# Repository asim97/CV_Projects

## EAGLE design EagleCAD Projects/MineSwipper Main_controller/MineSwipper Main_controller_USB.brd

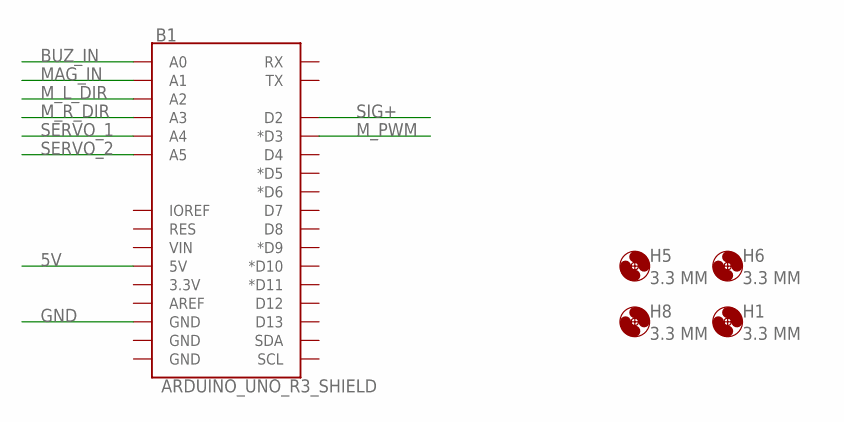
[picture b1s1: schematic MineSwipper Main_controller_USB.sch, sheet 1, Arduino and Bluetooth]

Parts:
B1: ARDUINO_UNO_R3_SHIELD; UNO_R3_SHIELD_NOLABELS_LOCK
H1, H5, H6, H8: 3.3 MM; 3,3

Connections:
5V: B1.5V; also elsewhere on the board
BUZ_IN: B1.A0; also elsewhere on the board
GND: B1.GND@2 (GND); also elsewhere on the board
MAG_IN: B1.A1; also elsewhere on the board
M_L_DIR: B1.A2; also elsewhere on the board
M_PWM: B1.D3 (*D3); also elsewhere on the board
M_R_DIR: B1.A3; also elsewhere on the board
SERVO_1: B1.A4; also elsewhere on the board
SERVO_2: B1.A5; also elsewhere on the board
SIG+: B1.D2; also elsewhere on the board

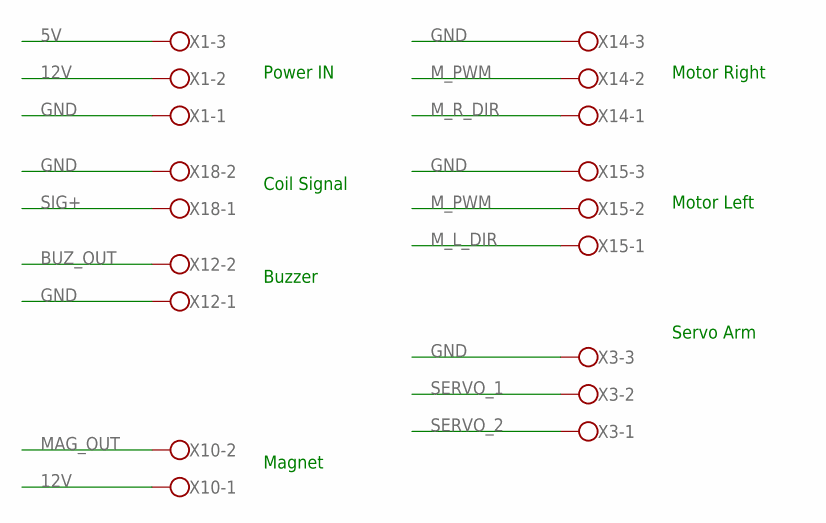
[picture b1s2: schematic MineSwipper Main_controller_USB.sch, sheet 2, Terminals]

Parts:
X1, X3, X14, X15: W237-103
X10, X12, X18: W237-102

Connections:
5V: X1.3; also elsewhere on the board
12V: X1.2, X10.1; also elsewhere on the board
BUZ_OUT: X12.2; also elsewhere on the board
GND: X1.1, X3.3, X12.1, X14.3, X15.3, X18.2; also elsewhere on the board
MAG_OUT: X10.2; also elsewhere on the board
M_L_DIR: X15.1; also elsewhere on the board
M_PWM: X14.2, X15.2; also elsewhere on the board
M_R_DIR: X14.1; also elsewhere on the board
SERVO_1: X3.2; also elsewhere on the board
SERVO_2: X3.1; also elsewhere on the board
SIG+: X18.1; also elsewhere on the board

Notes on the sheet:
Motor Right
Motor Left
Servo Arm
Power IN
Buzzer
Magnet
Coil Signal

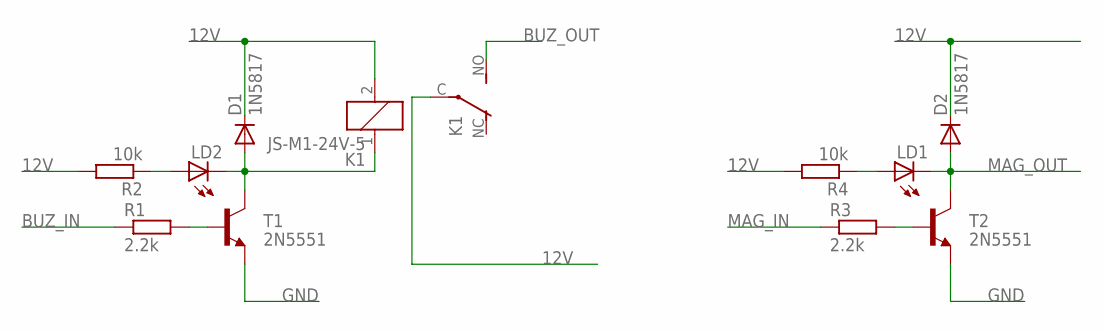
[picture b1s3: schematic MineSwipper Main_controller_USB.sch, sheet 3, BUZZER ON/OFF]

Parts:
D1, D2: 1N5817; DO41-10
K1: JS-M1-24V-5; JS-M
LD1, LD2: LED5MM
R1, R3: 2.2k; 0207/10
R2, R4: 10k; 0207/10
T1, T2: 2N5551; TO92-EBC-OVAL

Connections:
12V: D1.C, D2.C, K1.2, K1.C, R2.2, R4.2; also elsewhere on the board
BUZ_IN: R1.1; also elsewhere on the board
BUZ_OUT: K1.NO (S); also elsewhere on the board
GND: T1.E, T2.E; also elsewhere on the board
MAG_IN: R3.1; also elsewhere on the board
MAG_OUT: D2.A, LD1.K (C), T2.C; also elsewhere on the board
unnamed: R3.2, T2.B
unnamed: LD1.A, R4.1
unnamed: D1.A, K1.1, LD2.K (C), T1.C
unnamed: R1.2, T1.B
unnamed: LD2.A, R2.1

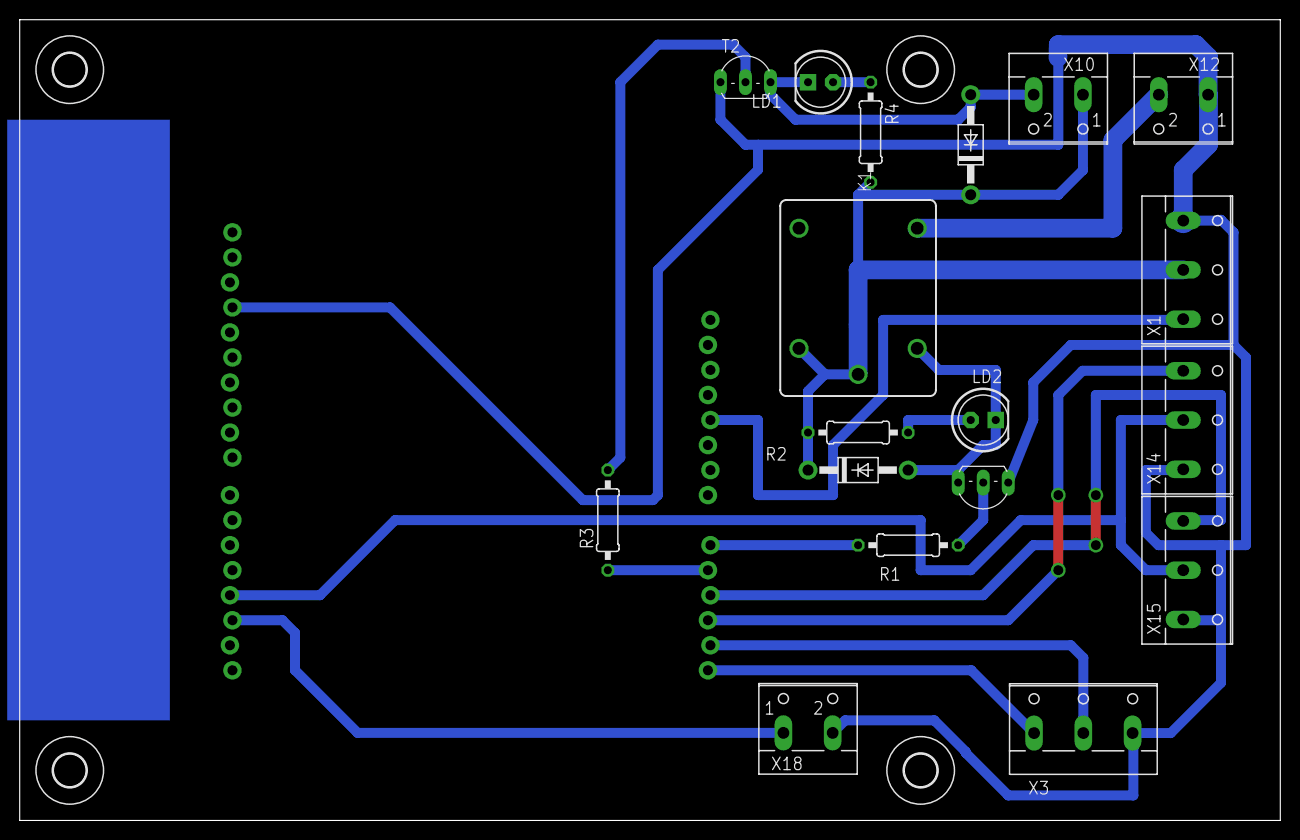
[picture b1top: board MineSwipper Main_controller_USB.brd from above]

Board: 2 copper layers, 127.9 x 81.3 mm, 23 parts (1 on the bottom side), 18 nets.

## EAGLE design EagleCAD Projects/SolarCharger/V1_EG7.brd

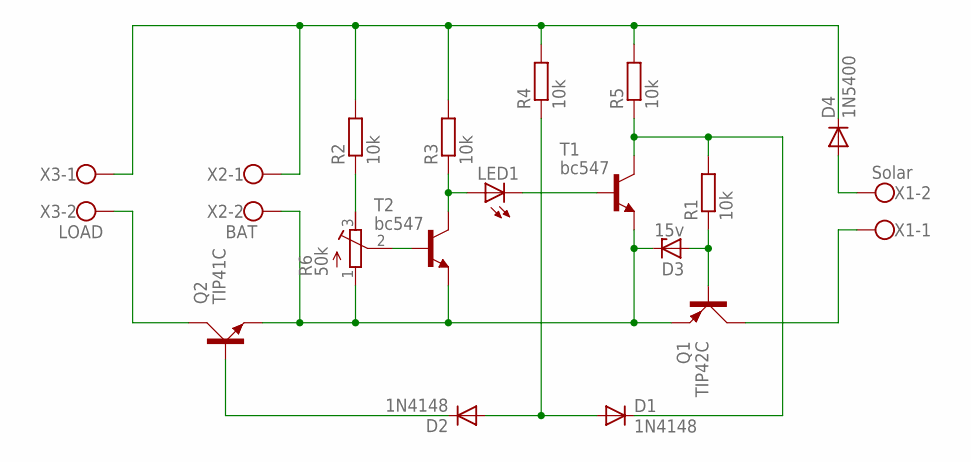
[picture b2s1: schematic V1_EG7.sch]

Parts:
D1, D2: 1N4148; DO35-10
D3: 15v; ZDIO-10
D4: 1N5400; DO201-15
LED1: LED5MM
Q1: TIP42C; TO220AV
Q2: TIP41C; TO220AV
R1, R2, R3, R4, R5: 10k; 0207/10
R6: 50k; RTRIM64W
T1, T2: bc547; TO92-CBE
X1: Solar; W237-102
X2: BAT; W237-102
X3: LOAD; W237-102

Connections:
GND: D3.C, Q1.E, Q2.E, R6.1 (A), T1.E, T2.E, X2.2
unnamed: R6.2 (S), T2.B
unnamed: R2.1, R6.3 (E)
unnamed: LED1.A, R3.1, T2.C
unnamed: LED1.K (C), T1.B
unnamed: D1.C, R1.2, R5.1, T1.C
unnamed: D3.A, Q1.B, R1.1
unnamed: D1.A, D2.A, R4.1
unnamed: Q2.C, X3.2
unnamed: Q1.C, X1.1
unnamed: D2.C, Q2.B
unnamed: D4.C, R2.2, R3.2, R4.2, R5.2, X2.1, X3.1
unnamed: D4.A, X1.2

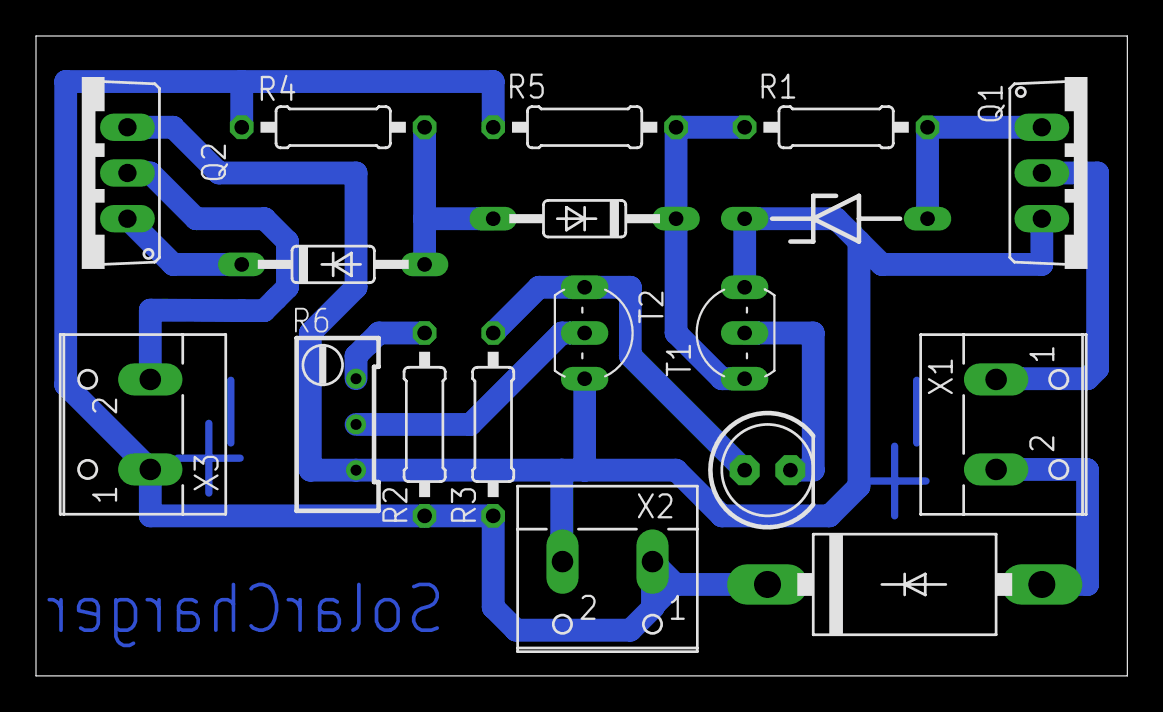
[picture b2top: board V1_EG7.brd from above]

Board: 2 copper layers, 60.6 x 35.5 mm, 18 parts (0 on the bottom side), 13 nets.

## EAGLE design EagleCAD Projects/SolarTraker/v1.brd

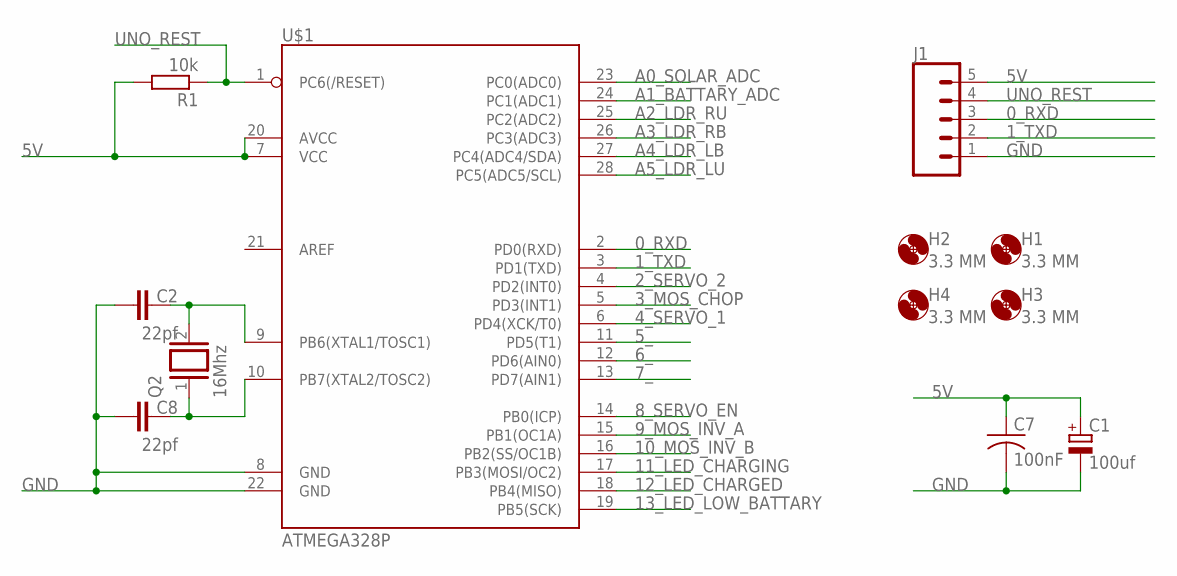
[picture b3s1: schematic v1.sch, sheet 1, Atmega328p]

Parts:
C1: 100uf; E3,5-8
C2, C8: 22pf; C050-030X075
C7: 100nF; C050-035X075
H1, H2, H3, H4: 3.3 MM; 3,3
J1: CONN_05JST-VERT; JST-5-PTH-VERT
Q2: 16Mhz; QS
R1: 10k; 0207/10
U$1: ATMEGA328P; DIL-28-3

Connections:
0_RXD: J1.3, U$1.2 (PD0(RXD))
1_TXD: J1.2, U$1.3 (PD1(TXD))
2_SERVO_2: U$1.4 (PD2(INT0)); also elsewhere on the board
3_MOS_CHOP: U$1.5 (PD3(INT1)); also elsewhere on the board
4_SERVO_1: U$1.6 (PD4(XCK/T0)); also elsewhere on the board
5V: C1.+, C7.1, J1.5, R1.2, U$1.7 (VCC), U$1.20 (AVCC); also elsewhere on the board
5_: U$1.11 (PD5(T1))
6_: U$1.12 (PD6(AIN0))
7_: U$1.13 (PD7(AIN1))
8_SERVO_EN: U$1.14 (PB0(ICP)); also elsewhere on the board
9_MOS_INV_A: U$1.15 (PB1(OC1A)); also elsewhere on the board
10_MOS_INV_B: U$1.16 (PB2(SS/OC1B)); also elsewhere on the board
11_LED_CHARGING: U$1.17 (PB3(MOSI/OC2)); also elsewhere on the board
12_LED_CHARGED: U$1.18 (PB4(MISO)); also elsewhere on the board
13_LED_LOW_BATTARY: U$1.19 (PB5(SCK)); also elsewhere on the board
A0_SOLAR_ADC: U$1.23 (PC0(ADC0)); also elsewhere on the board
A1_BATTARY_ADC: U$1.24 (PC1(ADC1)); also elsewhere on the board
A2_LDR_RU: U$1.25 (PC2(ADC2)); also elsewhere on the board
A3_LDR_RB: U$1.26 (PC3(ADC3)); also elsewhere on the board
A4_LDR_LB: U$1.27 (PC4(ADC4/SDA)); also elsewhere on the board
A5_LDR_LU: U$1.28 (PC5(ADC5/SCL)); also elsewhere on the board
GND: C1.-, C2.1, C7.2, C8.1, J1.1, U$1.8 (GND), U$1.22 (GND); also elsewhere on the board
unnamed: C2.2, Q2.2, U$1.9 (PB6(XTAL1/TOSC1))
unnamed: C8.2, Q2.1, U$1.10 (PB7(XTAL2/TOSC2))
UNO_REST: J1.4, R1.1, U$1.1 (PC6(/RESET))

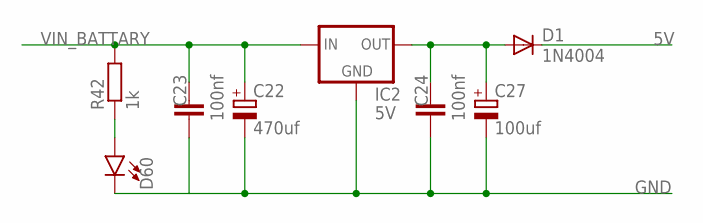
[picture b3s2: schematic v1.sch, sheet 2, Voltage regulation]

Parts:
C22: 470uf; E3,5-8
C23, C24: 100nf; C050-030X075
C27: 100uf; E3,5-8
D1: 1N4004; DO41-10
D60: LED5MM; LED_5MM
IC2: 5V; 78XXL
R42: 1k; 0207/10

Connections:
5V: D1.C; also elsewhere on the board
GND: C22.-, C23.1, C24.1, C27.-, D60.K (C), IC2.GND; also elsewhere on the board
unnamed: C24.2, C27.+, D1.A, IC2.OUT
unnamed: D60.A, R42.1
VIN_BATTARY: C22.+, C23.2, IC2.IN, R42.2; also elsewhere on the board

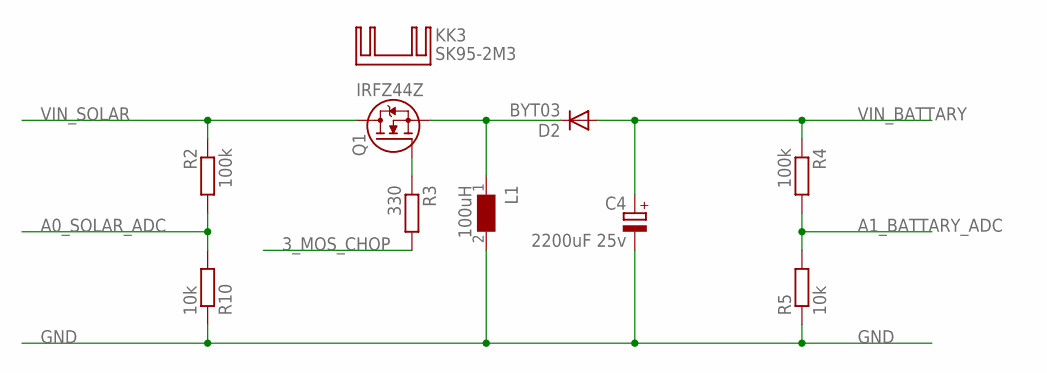
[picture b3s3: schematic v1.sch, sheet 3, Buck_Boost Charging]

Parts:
C4: 2200uF 25v; E5-13
D2: BYT03; DO27-15
KK3: SK95-2M3
L1: 100uH; WE-ZB
Q1: IRFZ44Z; TO220V
R2, R4: 100k; 0207/10
R3: 330; 0207/10
R5, R10: 10k; 0207/10

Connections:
3_MOS_CHOP: R3.2; also elsewhere on the board
A0_SOLAR_ADC: R2.2, R10.2; also elsewhere on the board
A1_BATTARY_ADC: R4.2, R5.2; also elsewhere on the board
GND: C4.-, L1.2, R5.1, R10.1; also elsewhere on the board
unnamed: D2.C, L1.1, Q1.3 (S)
unnamed: Q1.1 (G), R3.1
VIN_BATTARY: C4.+, D2.A, R4.1; also elsewhere on the board
VIN_SOLAR: Q1.2 (D), R2.1; also elsewhere on the board

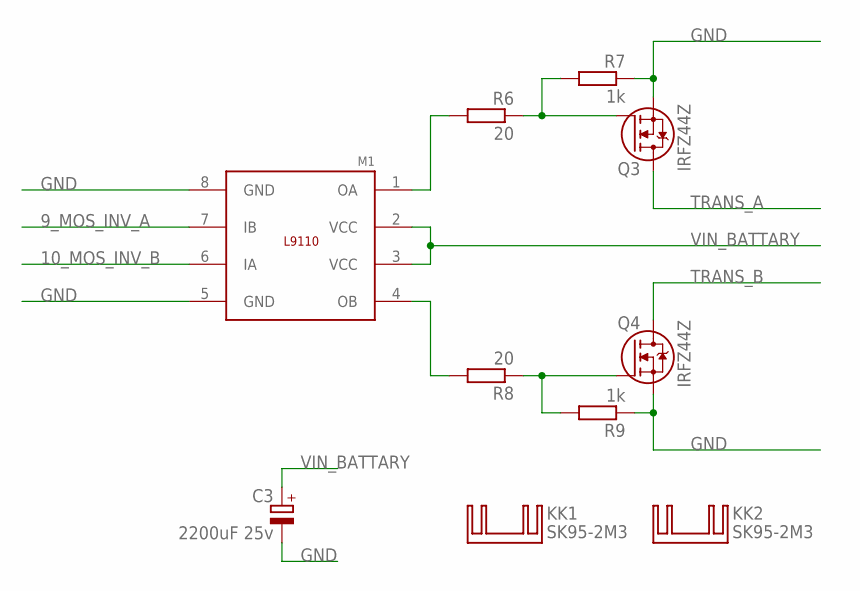
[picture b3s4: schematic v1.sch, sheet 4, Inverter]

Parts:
C3: 2200uF 25v; E5-13
KK1, KK2: SK95-2M3
M1: L9110; SO8P
Q3, Q4: IRFZ44Z; TO220V
R6, R8: 20; 0207/10
R7, R9: 1k; 0207/10

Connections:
9_MOS_INV_A: M1.7 (IB); also elsewhere on the board
10_MOS_INV_B: M1.6 (IA); also elsewhere on the board
GND: C3.-, M1.5 (GND), M1.8 (GND), Q3.3 (S), Q4.3 (S), R7.1, R9.1; also elsewhere on the board
unnamed: Q3.1 (G), R6.1, R7.2
unnamed: M1.4 (OB), R8.2
unnamed: Q4.1 (G), R8.1, R9.2
unnamed: M1.1 (OA), R6.2
TRANS_A: Q3.2 (D); also elsewhere on the board
TRANS_B: Q4.2 (D); also elsewhere on the board
VIN_BATTARY: C3.+, M1.2 (VCC), M1.3 (VCC); also elsewhere on the board

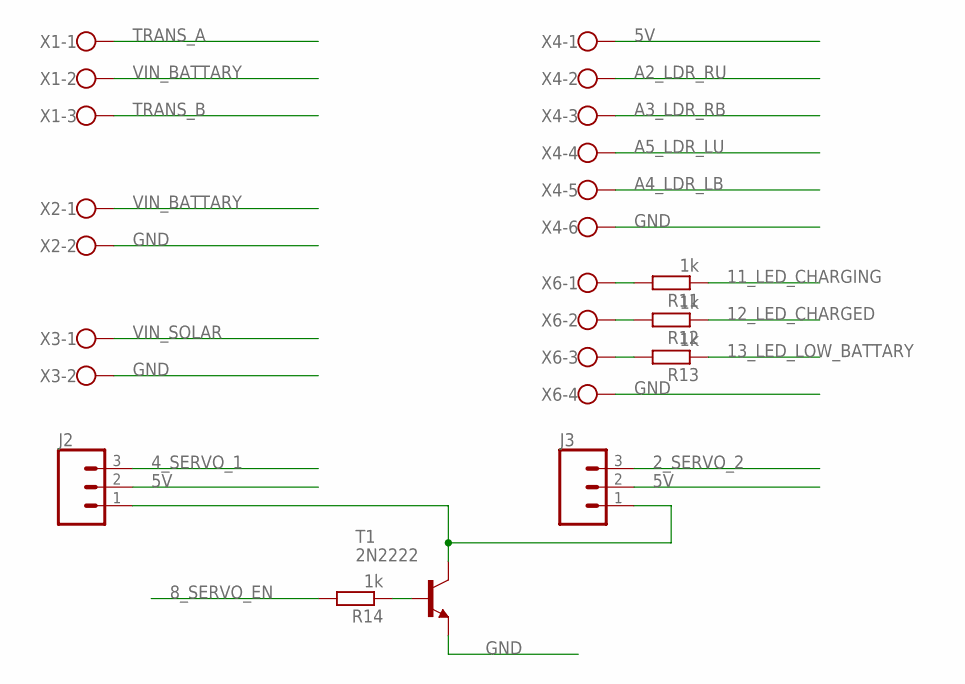
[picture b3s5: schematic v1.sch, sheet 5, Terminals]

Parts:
J2, J3: CONN_03JST-PTH-VERT; JST-3-PTH-VERT
R11, R12, R13, R14: 1k; 0207/10
T1: 2N2222; TO92-EBC-OVAL
X1: W237-103
X2, X3: W237-102
X4: W237-6
X6: W237-4

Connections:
2_SERVO_2: J3.3; also elsewhere on the board
4_SERVO_1: J2.3; also elsewhere on the board
5V: J2.2, J3.2, X4.1; also elsewhere on the board
8_SERVO_EN: R14.2; also elsewhere on the board
11_LED_CHARGING: R11.1; also elsewhere on the board
12_LED_CHARGED: R12.1; also elsewhere on the board
13_LED_LOW_BATTARY: R13.1; also elsewhere on the board
A2_LDR_RU: X4.2; also elsewhere on the board
A3_LDR_RB: X4.3; also elsewhere on the board
A4_LDR_LB: X4.5; also elsewhere on the board
A5_LDR_LU: X4.4; also elsewhere on the board
GND: T1.E, X2.2, X3.2, X4.6, X6.4; also elsewhere on the board
unnamed: R13.2, X6.3
unnamed: R12.2, X6.2
unnamed: R11.2, X6.1
unnamed: R14.1, T1.B
unnamed: J2.1, J3.1, T1.C
TRANS_A: X1.1; also elsewhere on the board
TRANS_B: X1.3; also elsewhere on the board
VIN_BATTARY: X1.2, X2.1; also elsewhere on the board
VIN_SOLAR: X3.1; also elsewhere on the board

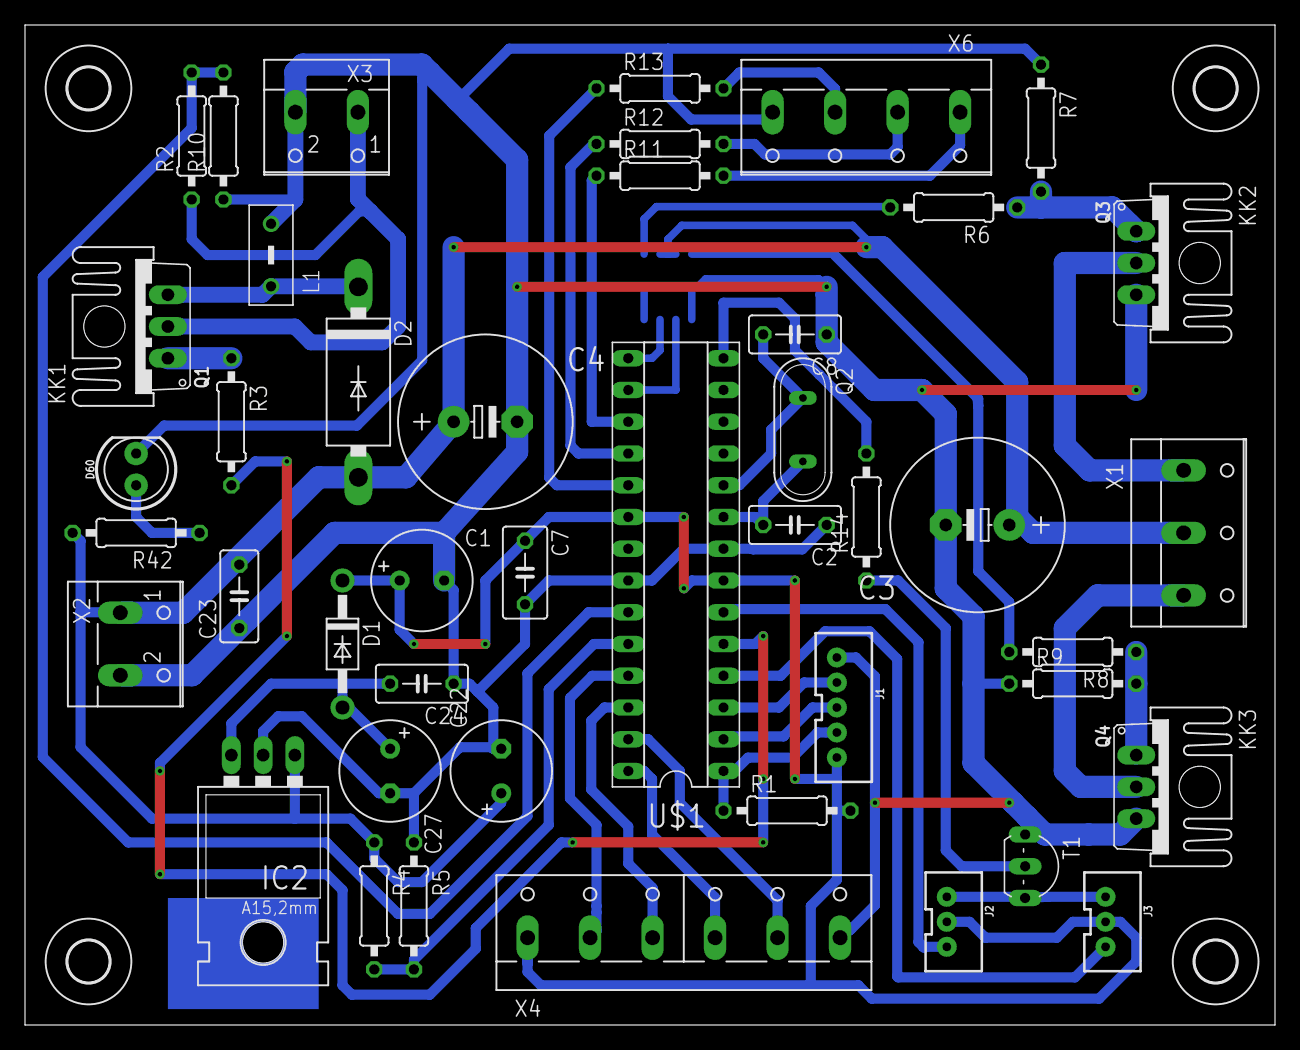
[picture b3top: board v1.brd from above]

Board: 2 copper layers, 100.0 x 80.0 mm, 52 parts (1 on the bottom side), 39 nets.

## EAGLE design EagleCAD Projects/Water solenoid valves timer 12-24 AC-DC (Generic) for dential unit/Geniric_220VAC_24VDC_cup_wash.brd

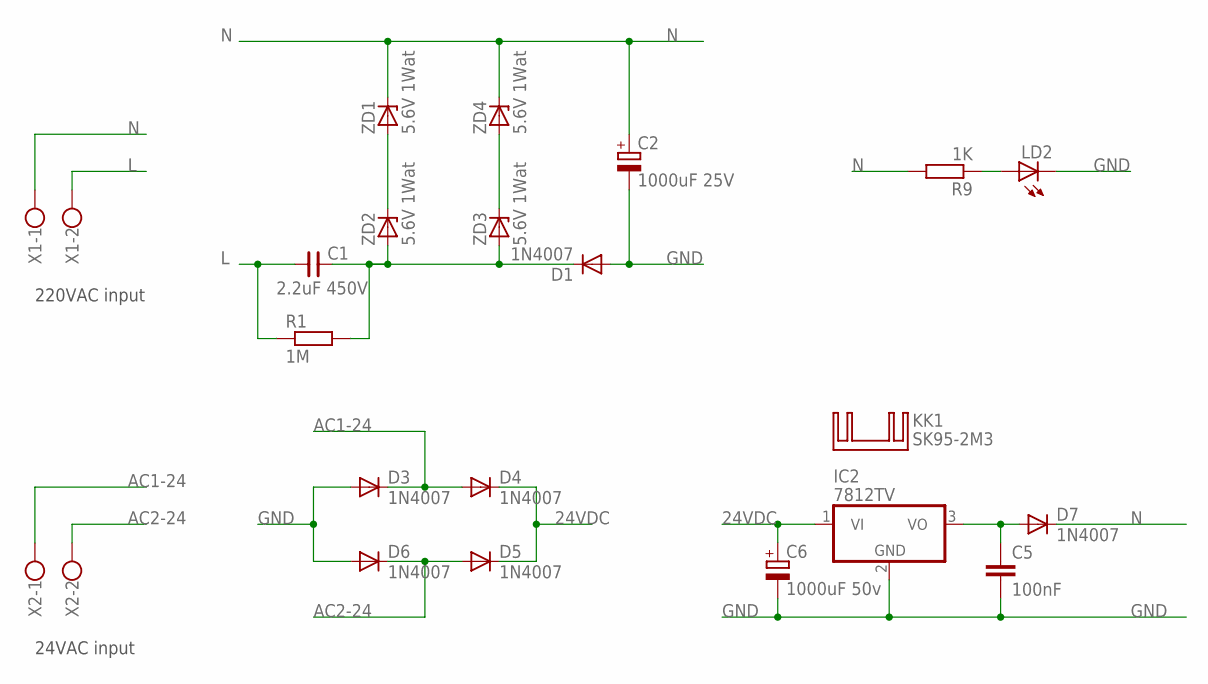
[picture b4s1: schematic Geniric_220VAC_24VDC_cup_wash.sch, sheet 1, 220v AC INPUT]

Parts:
C1: 2.2uF 450V; C150-190X070
C2: 1000uF 25V; E5-8,5
C5: 100nF; C050-025X075
C6: 1000uF 50v; E5-13
D1, D3, D4, D5, D6, D7: 1N4007; DO41-10
IC2: 7812TV; TO220V
KK1: SK95-2M3
LD2: LED5MM
R1: 1M; 0207/10
R9: 1K; 0207/10
X1, X2: W237-102
ZD1, ZD2, ZD3, ZD4: 5.6V 1Wat; DO35Z10

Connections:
24VDC: C6.+, D4.C, D5.C, IC2.1 (VI); also elsewhere on the board
AC1-24: D3.C, D4.A, X2.1; also elsewhere on the board
AC2-24: D5.A, D6.C, X2.2; also elsewhere on the board
GND: C2.-, C5.2, C6.-, D1.A, D3.A, D6.A, IC2.2 (GND), LD2.K (C); also elsewhere on the board
L: C1.1, R1.1, X1.2; also elsewhere on the board
N: C2.+, D7.C, R9.2, X1.1, ZD1.C, ZD4.C; also elsewhere on the board
unnamed: C1.2, D1.C, R1.2, ZD2.A, ZD3.A
unnamed: ZD1.A, ZD2.C
unnamed: ZD3.C, ZD4.A
unnamed: LD2.A, R9.1
NDDD: C5.1, D7.A, IC2.3 (VO)

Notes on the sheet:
220VAC input
24VAC input

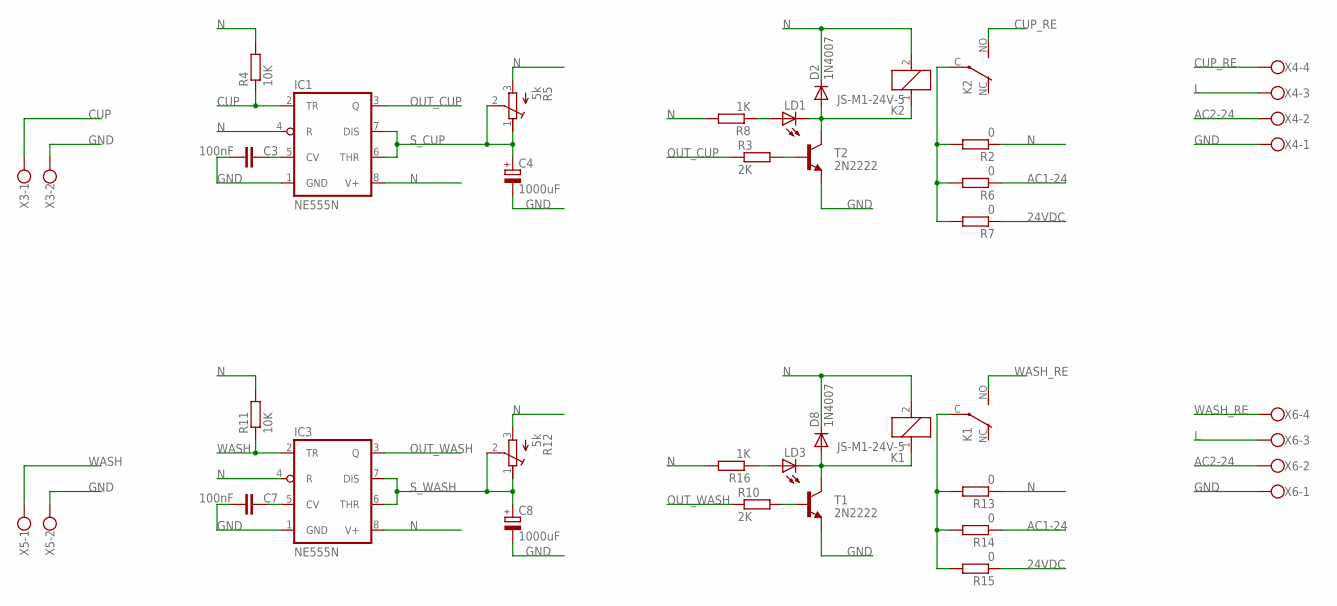
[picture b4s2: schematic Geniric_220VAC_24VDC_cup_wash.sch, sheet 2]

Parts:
C3, C7: 100nF; C050-025X075
C4, C8: 1000uF; E5-8,5
D2, D8: 1N4007; DO41-10
IC1, IC3: NE555N; DIL08-ROUND
K1, K2: JS-M1-24V-5; JS-M
LD1, LD3: LED5MM
R2, R6, R7, R13, R14, R15: 0; 0207/10
R3, R10: 2K; 0207/10
R4, R11: 10K; 0207/10
R5, R12: 5k; RTRIMT93XA
R8, R16: 1K; 0207/10
T1, T2: 2N2222; TO92-EBC-OVAL
X3, X5: W237-102
X4, X6: W237-4

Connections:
24VDC: R7.1, R15.1; also elsewhere on the board
AC1-24: R6.1, R14.1; also elsewhere on the board
AC2-24: X4.2, X6.2; also elsewhere on the board
CUP: IC1.2 (TR), R4.1, X3.1
CUP_RE: K2.NO (S), X4.4
GND: C3.2, C4.-, C7.2, C8.-, IC1.1 (GND), IC3.1 (GND), T1.E, T2.E, X3.2, X4.1, X5.2, X6.1; also elsewhere on the board
L: X4.3, X6.3; also elsewhere on the board
N: D2.C, D8.C, IC1.4 (R), IC1.8 (V+), IC3.4 (R), IC3.8 (V+), K1.2, K2.2, R2.1, R4.2, R5.3 (A), R8.2, R11.2, R12.3 (A), R13.1, R16.2; also elsewhere on the board
unnamed: R3.2, T2.B
unnamed: C3.1, IC1.5 (CV)
unnamed: D2.A, K2.1, LD1.K (C), T2.C
unnamed: C7.1, IC3.5 (CV)
unnamed: LD1.A, R8.1
unnamed: K2.C, R2.2, R6.2, R7.2
unnamed: D8.A, K1.1, LD3.K (C), T1.C
unnamed: R10.2, T1.B
unnamed: K1.C, R13.2, R14.2, R15.2
unnamed: LD3.A, R16.1
OUT_CUP: IC1.3 (Q), R3.1
OUT_WASH: IC3.3 (Q), R10.1
S_CUP: C4.+, IC1.6 (THR), IC1.7 (DIS), R5.1 (E), R5.2 (S)
S_WASH: C8.+, IC3.6 (THR), IC3.7 (DIS), R12.1 (E), R12.2 (S)
WASH: IC3.2 (TR), R11.1, X5.1
WASH_RE: K1.NO (S), X6.4

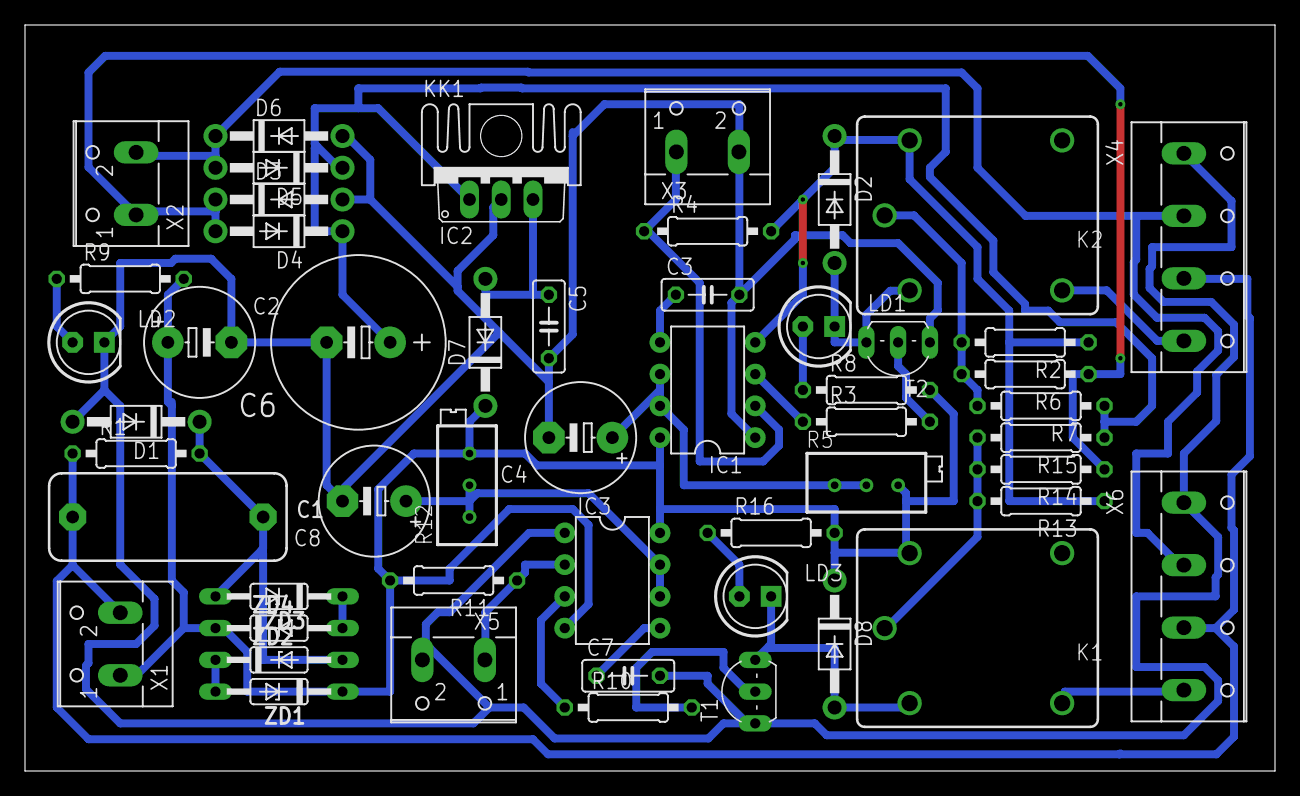
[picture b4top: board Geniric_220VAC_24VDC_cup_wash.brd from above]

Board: 2 copper layers, 100.0 x 59.7 mm, 53 parts (0 on the bottom side), 29 nets.

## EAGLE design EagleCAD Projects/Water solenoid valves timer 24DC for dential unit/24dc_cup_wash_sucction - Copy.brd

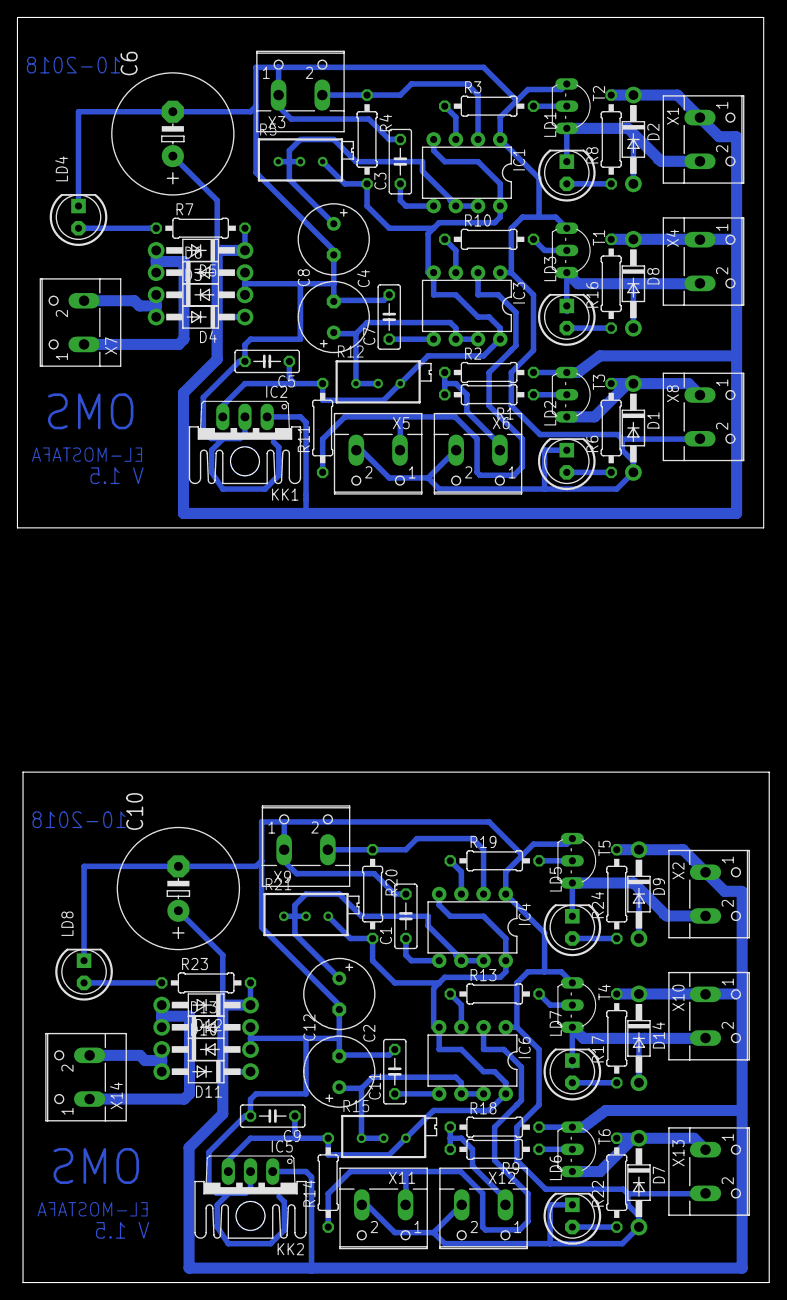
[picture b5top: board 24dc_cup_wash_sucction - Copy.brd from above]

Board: 2 copper layers, 86.0 x 144.8 mm, 86 parts (0 on the bottom side), 48 nets.

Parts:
C1, C3, C5, C7, C9, C11: 100nF; C050-025X075
C2, C4, C8, C12: 100uF; E3,5-8
C6, C10: 1000uF 50v; E5-13
D1, D2, D7, D8, D9, D14: 1N5817; DO41-10
D3, D4, D5, D6, D10, D11, D12, D13: 1N4007; DO41-10
IC1, IC3, IC4, IC6: NE555N; DIL08-ROUND
IC2, IC5: 7812TV; TO220V
KK1, KK2: SK95-2M3
LD1, LD2, LD3, LD4, LD5, LD6, LD7, LD8: LED5MM
R1, R3, R9, R10, R13, R19: 2.2k; 0207/10
R2, R4, R11, R14, R18, R20: 10K; 0207/10
R5, R12, R15, R21: 100k; RTRIMT93XA
R6, R7, R8, R16, R17, R22, R23, R24: 10k; 0207/10
T1, T2, T4, T5: 2N5551; TO92-EBC-OVAL
T3, T6: 2N5401; TO92-EBC
X1, X2, X3, X4, X5, X6, X7, X8, X9, X10, X11, X12, X13, X14: W237-102

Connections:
12VDC: C5.1, IC1.4, IC1.8, IC2.3, IC3.4, IC3.8, R4.2, R5.3, R11.2, R12.3
12VDC1: C9.1, IC4.4, IC4.8, IC5.3, IC6.4, IC6.8, R14.2, R15.3, R20.2, R21.3
12VDC_IN: C6.+, D2.C, D4.C, D5.C, D8.C, IC2.1, R2.2, R7.2, R8.2, R16.2, T3.E, X1.1, X4.1
12VDC_IN1: C10.+, D9.C, D11.C, D12.C, D14.C, IC5.1, R17.2, R18.2, R23.2, R24.2, T6.E, X2.1, X10.1
AC1-1: D12.A, D13.C, X14.1
AC1-24: D5.A, D6.C, X7.1
AC2-1: D10.C, D11.A, X14.2
AC2-24: D3.C, D4.A, X7.2
CUP: IC1.2, R4.1, X3.2
CUP1: IC4.2, R20.1, X9.2
GND: C3.2, C4.-, C5.2, C6.-, C7.2, C8.-, D1.A, D3.A, D6.A, IC1.1, IC2.2, IC3.1, LD2.K, LD4.K, T1.E, T2.E, X3.1, X5.2, X6.2, X8.2
GND1: C1.2, C2.-, C9.2, C10.-, C11.2, C12.-, D7.A, D10.A, D13.A, IC4.1, IC5.2, IC6.1, LD6.K, LD8.K, T4.E, T5.E, X9.1, X11.2, X12.2, X13.2
unnamed: R3.2, T2.B
unnamed: C3.1, IC1.5
unnamed: D2.A, LD1.K, T2.C, X1.2
unnamed: LD8.A, R23.1
unnamed: C7.1, IC3.5
unnamed: LD1.A, R8.1
unnamed: R1.1, T3.B
unnamed: LD4.A, R7.1
unnamed: LD2.A, R6.1
unnamed: C1.1, IC4.5
unnamed: D8.A, LD3.K, T1.C, X4.2
unnamed: R10.2, T1.B
unnamed: D9.A, LD5.K, T5.C, X2.2
unnamed: LD3.A, R16.1
unnamed: R19.2, T5.B
unnamed: LD5.A, R24.1
unnamed: C11.1, IC6.5
unnamed: D14.A, LD7.K, T4.C, X10.2
unnamed: R13.2, T4.B
unnamed: LD7.A, R17.1
unnamed: R9.1, T6.B
unnamed: LD6.A, R22.1
NS1: D1.C, R6.2, T3.C, X8.1
NS2: D7.C, R22.2, T6.C, X13.1
OUT_CUP: IC1.3, R3.1
OUT_CUP1: IC4.3, R19.1
OUT_WASH: IC3.3, R10.1
OUT_WASH1: IC6.3, R13.1
SUC: R1.2, R2.1, X6.1
SUC1: R9.2, R18.1, X12.1
S_CUP: C4.+, IC1.6, IC1.7, R5.1, R5.2
S_CUP1: C2.+, IC4.6, IC4.7, R21.1, R21.2
S_WASH: C8.+, IC3.6, IC3.7, R12.1, R12.2
S_WASH1: C12.+, IC6.6, IC6.7, R15.1, R15.2
WASH: IC3.2, R11.1, X5.1
WASH1: IC6.2, R14.1, X11.1

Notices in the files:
parts and their libraries:
SparkFun-LED: Licensing: Creative Commons ShareAlike 4.0 International - https://creativecommons.org/licenses/by-sa/4.0
wuerth_elektronik_eisos__v6.5: Copyright: Würth Elektronik
